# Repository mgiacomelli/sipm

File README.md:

**This page is obsolete.  A greatly improved design is available here: https://github.com/OpenSiPM/sipm-bias-control**

The updated design has higher dynamic range, lower noise, higher bandwidth and includes the bias generation, power supplies and low pass filter.  

# Introduction

These are the design files for the SIPM amplifier described in M. G. Giacomelli, "Evaluation of silicon photomultipliers for multiphoton and laser scanning microscopy," J. Biomed. Opt. 24, 1 (2019) available from https://www.spiedigitallibrary.org/journals/journal-of-biomedical-optics/volume-24/issue-10/106503/Evaluation-of-silicon-photomultipliers-for-multiphoton-and-laser-scanning-microscopy/10.1117/1.JBO.24.10.106503.full?SSO=1.  

The design is a relatively low cost, single photon sensitive fluorescense detector using the S14420 silicon photomultiplier from Hamamatsu, which is a TO-5 mounted detector with high QE from 500-700nm.  Compared to a PMT the S14420 has higher effective quantum efficiency (especially above 600nm) but higher dark counts.  

# Files

The 'Old Gerbers' folder contains the exact gerber files used to manufacture the boards in the manuscript.  The Improved Design folder has KiCAD and gerber files for an updated version of that design that has a few improvements.  In addition, since the design files are present, you can make changes to the design as needed using the open source EDA software KiCAD.  If you only want to make a board, you can upload either set of Gerber files directly to JLCPCB, SEEED, etc.  

# Setting up KiCAD

This project was designed using the current development (5.99) branch of KiCAD, so you must be running that or newer.  Windows builds are available here: 
https://kicad-downloads.s3.cern.ch/index.html?prefix=windows/nightly/

# Ordering boards

Go to https://jlcpcb.com/ or https://www.seeedstudio.com/fusion_pcb.html or the service of your choice, upload the Gerber files, choose 2 layer, and pay.  At present prices, 10 boards will cost about 15-20 dollars shipped to most of the world.  

# Bill of materials

An interactive BOM tool is available here to make placing and ordering compnents easy:  http://htmlpreview.github.io/?https://github.com/mgiacomelli/sipm/blob/master/Improved%20Design/KiCAD/bom/ibom.html

In addition, you will need the matching power cable.  The part is DF13-5S-1.25C, and unless you have the matching crimp tool, you will need 5x H4BBT-10112-R8 pre-crimped leads.  I recommend getting multiple colors as mixing up the wires will destroy your board.  

# Assembly

The easiest way to assemble these boards is using solder paste and a reflow oven.  The inexpensive T-962 clones on Amazon will work fine for simple boards such as this.  Alternatively, they can also be manually soldered.  The design uses a mix of 0402 and larger parts, which can be challenging to solder with the wrong tools.  A ~0.6-1.2mm diameter chissel type soldering tip, high quality no clean flux such as amtech nc-559-v2-tf, 40/60 lead solder, and good tweezer such as Hakko CHP 5-SA or equivilent are strongly recommended if reflow is not used. These are inexpensive and readily available on Amazon. 

# Circuit design

Both the old and improved designs are a 1500 V/A transimpedance amplifier paired with a pole zero compensation (PZC) circuit.  Both PZCs have the same frequency cut on.  The old design uses a capacitive PZC.  While more obvious, this design is problematic because the capacitance of the PZC loads the amplifier.  The original design put an isolation resistor before the capacitance, but this design halves the gain and is less stable.  The improved design implements the same filter but using an inductor.  As a result the resistor and reactive element are flipped, meaning that the opamp is not directly connected to the reactive element and so the isolation resistor is not needed. Therefore gain is doubled.  Further since the PZC resistance is larger, stability is improved.  

# PZC

The values of L1, R5 and R6 define the PZC cut on and amplitude.  These values were near optimal for a previous board iteration, however, the PZC is very sensitive to the exact values so you may find that to hit very high bandwidth (40-50 MHz) or very flat pass band that the values must be adjusted.  Essentially the PZC is adding a gain that compensates for the frequency roll off caused by the RC time constant associated with the individual SIPM cell recharge through the quenching resistors, so adjusting L1 changes at what frequency the added gain kicks in, while changing the values of the resistors lets you change the strength of that gain.  By setting the values carefully, you can cancel out the recharge time of the individual APDs and greatly extend the bandwidth of the detector, often by a factor of 10 or more.  

A more intuitive explination of the PZC method is described in this article:
A. Gola, C. Piemonte, and A. Tarolli, "Analog circuit for timing measurements with large area sipms coupled to lyso crystals," IEEE Trans. Nucl. Sci. 60, 1296–1302 (2013).

# Low pass filter

It is important to add an external low pass filter, either in your ADC or inline with it to reject out of band noise.  If you do not have a suitable lowpass on your ADC, the minicircuits BLP-25 is a reasonable choice with relatively little group delay in the pass band:  https://www.minicircuits.com/WebStore/dashboard.html?model=BLP-25%2B

The bandwidth of a laser scanner is 0.312 times the scan velocity (in meters per second) divided by the spot size (also in meters).  It is a good idea to reduce the bandwidth of the detector as needed with a smaller low pass filter if you do not require 25 MHz at your scan speed.  This will reduce electronic noise.    

# Gain

Total transimpedance gain (as configured, you can adjust it) is 1500 ohms.  There is an additional factor of 2 gain in the OPA842 stage, but this merely compensates for the attenuation caused by the 50 Ohm output impedance.  In addition, the PZC attenautes by a factor of R6/R5 (about 8:1).  Thus peak ampltidue per photon at +5Vbr should be about 4.5mV.  

# Mounting

The entire board is 1 inch across and will mount in an SM1 lens tube:  https://www.thorlabs.com/newgrouppage9.cfm?objectgroup_id=3307

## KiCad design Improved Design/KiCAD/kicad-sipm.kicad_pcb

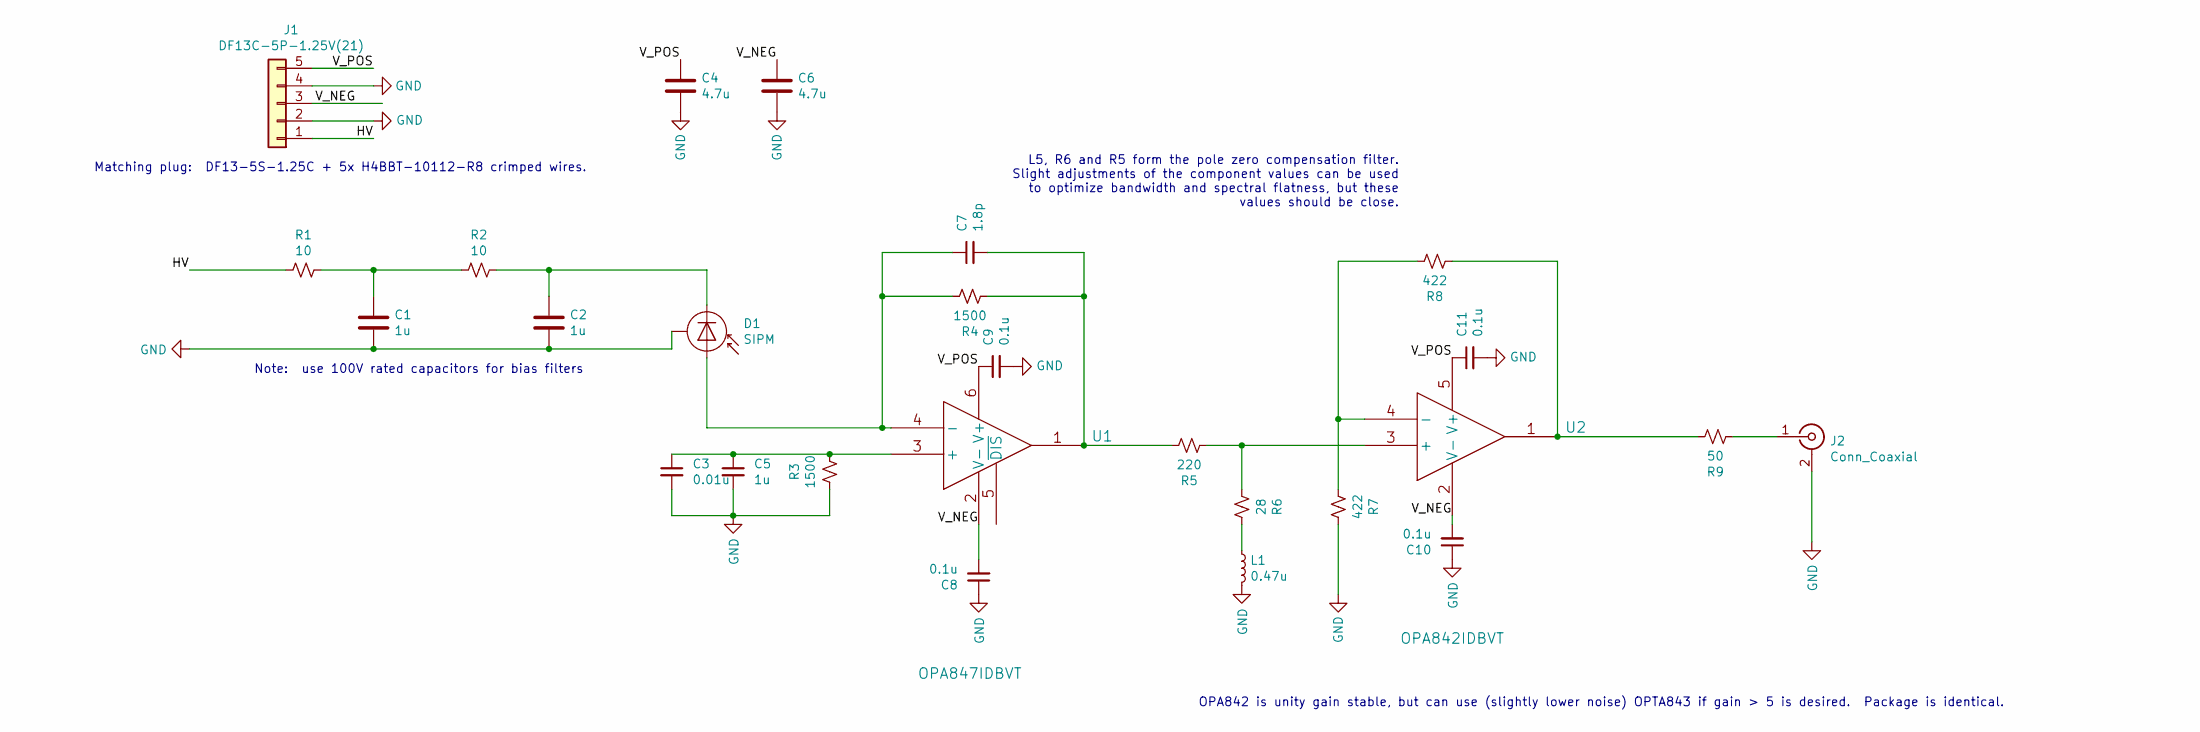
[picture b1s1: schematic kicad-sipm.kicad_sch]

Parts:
C1, C2: 1u; C_1206_3216Metric
C3: 0.01u; C_0402_1005Metric
C4, C6: 4.7u; C_1206_3216Metric
C5: 1u; C_0402_1005Metric
C7: 1.8p; C_0402_1005Metric
C8, C9, C10, C11: 0.1u; C_0402_1005Metric
D1: SIPM; S14420
J1: DF13C-5P-1.25V(21); DF13C-5P-1.25V21; Digikey Part H126001CT-ND
J2: Conn_Coaxial; SMB_Jack_Vertical
L1: 0.47u; L_0603_1608Metric
R1, R2: 10; R_0402_1005Metric
R3, R4: 1500; R_0402_1005Metric
R5: 220; R_0402_1005Metric
R6: 28; R_0402_1005Metric
R7, R8: 422; R_0402_1005Metric
R9: 50; R_0402_1005Metric
U1: OPA847IDBVT
U2: OPA842IDBVT; OPA843IDBVT

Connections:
/HV: J1.1, R1.1
/V_NEG: C6.1, C8.2, C10.2, J1.3, U1.2 (V-), U2.2 (V-)
/V_POS: C4.1, C9.1, C11.1, J1.5, U1.6 (V+), U2.5 (V+)
GND: C1.2, C2.2, C3.2, C4.2, C5.2, C6.2, C8.1, C9.2, C10.1, C11.2, D1.3 (CASE), J1.2, J1.4, J2.2 (Ext), L1.2, R3.1, R7.2
unnamed: C1.1, R1.2, R2.1
unnamed: C2.1, D1.1 (K), R2.2
unnamed: C3.1, C5.1, R3.2, U1.3 (+)
unnamed: C7.1, D1.2 (A), R4.2, U1.4 (-)
unnamed: C7.2, R4.1, R5.2, U1.1
unnamed: J2.1 (In), R9.1
unnamed: L1.1, R6.2
unnamed: R5.1, R6.1, U2.3 (+)
unnamed: R7.1, R8.2, U2.4 (-)
unnamed: R8.1, R9.2, U2.1

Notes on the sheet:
Note: use 100V rated capacitors for bias filters
Matching plug: DF13-5S-1.25C + 5x H4BBT-10112-R8 crimped wires.
OPA842 is unity gain stable, but can use (slightly lower noise) OPTA843 if gain > 5 is desired. Package is identical.
L5, R6 and R5 form the pole zero compensation filter. Slight adjustments of the component values can be used to optimize bandwidth and spectral flatness, but these values should be close.

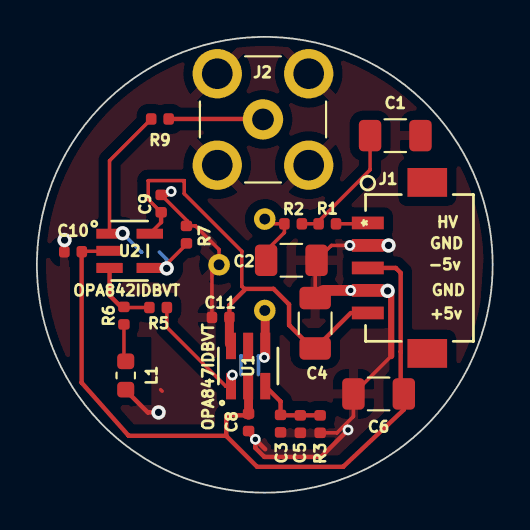
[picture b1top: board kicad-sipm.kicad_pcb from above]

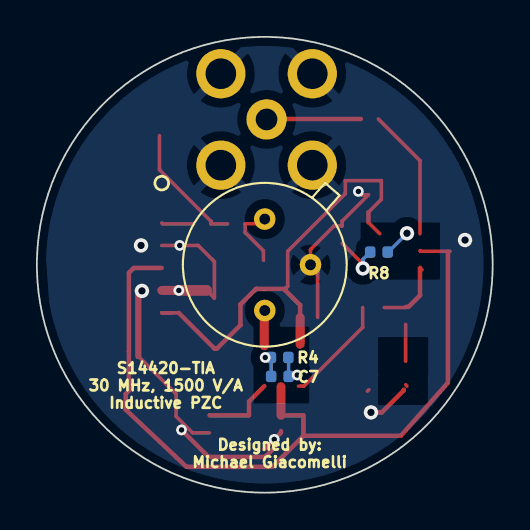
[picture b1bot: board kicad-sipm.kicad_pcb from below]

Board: 2 copper layers, 25.3 x 25.3 mm, 26 parts (4 on the bottom side), 14 nets.

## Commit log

2019-09-09 Check in Gerber files for the TIA v3 PCB design.
2019-09-09 Add a brief readme
2019-09-11 Add BOM for the TIAv3 project.
2020-09-12 Add KiCAD design files for updated TIA design
2020-09-12 Set project output to JLCPCB recommended settings
2020-09-12 Commit Gerbers and fix some labeling mistakes
2020-09-12 Add part number for the pin header and the matching plug
2020-09-12 Update labels one more time.
2020-09-13 Correct PZC values
2020-09-13 Add render.
2020-09-13 Add 3d model for connector

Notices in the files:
parts and their libraries:
Copyright 2016 Accelerated Designs. All rights reserved.
